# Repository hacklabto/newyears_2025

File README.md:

# Hacky New Years

Hacky New Years is an annual collaborative project, where a hackerspace's 
members produce an artifact in quantity to be sent to other spaces. This can 
be a piece art, electronics, or literature. Whatever the collaborators of 
that year come to consensus on. 

https://knowledge.hacklab.to/wiki/Hacky_New_Years

## Hacklab's artifact for 2025 
A collaborative, interdisciplinary technology based art project.

https://knowledge.hacklab.to/wiki/Hacky_New_Years/2025

This repository contains the software code and other artifacts used in the 
production of the final piece sent for 2025.

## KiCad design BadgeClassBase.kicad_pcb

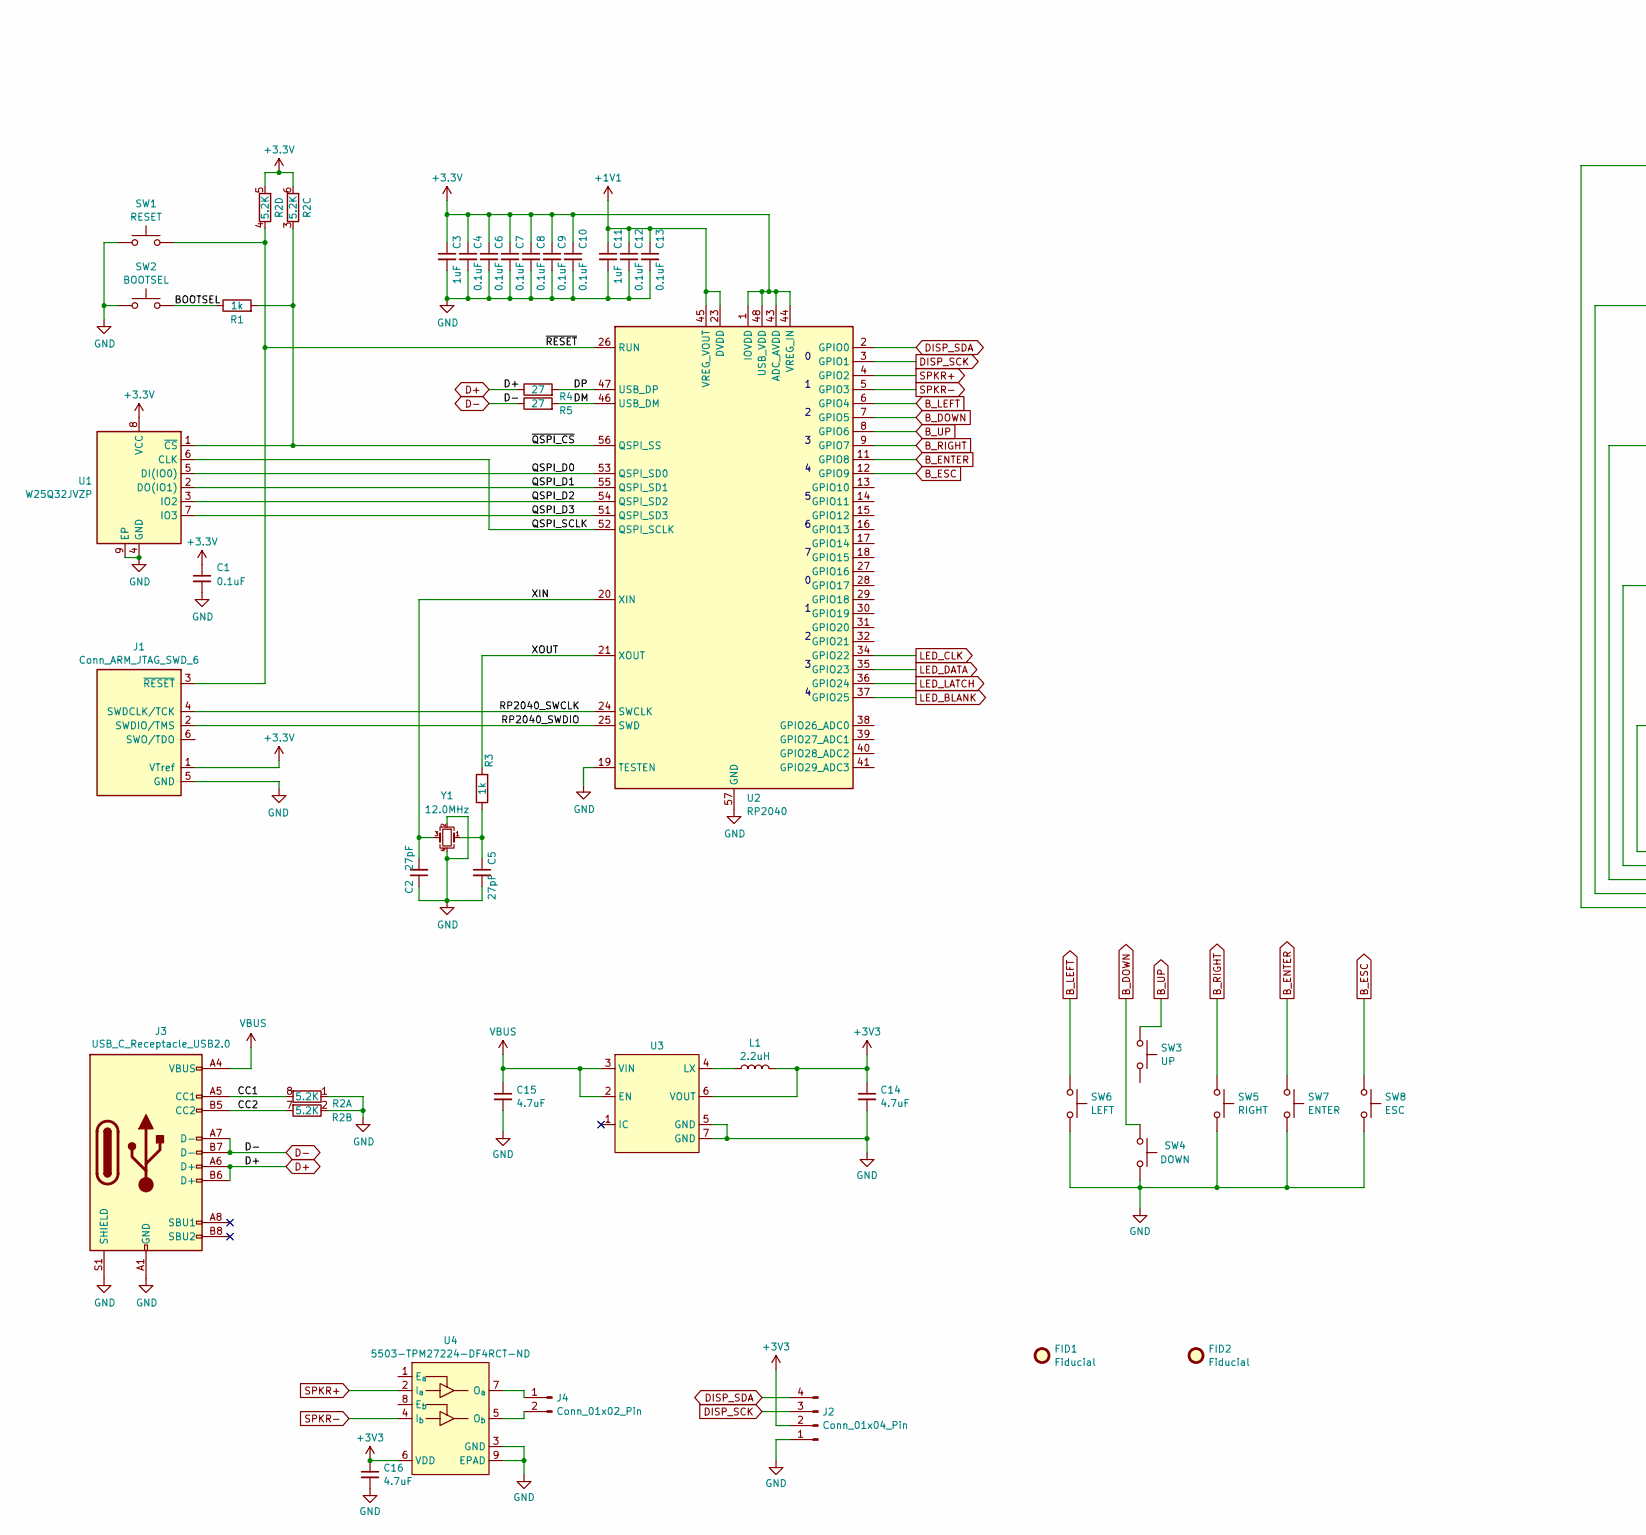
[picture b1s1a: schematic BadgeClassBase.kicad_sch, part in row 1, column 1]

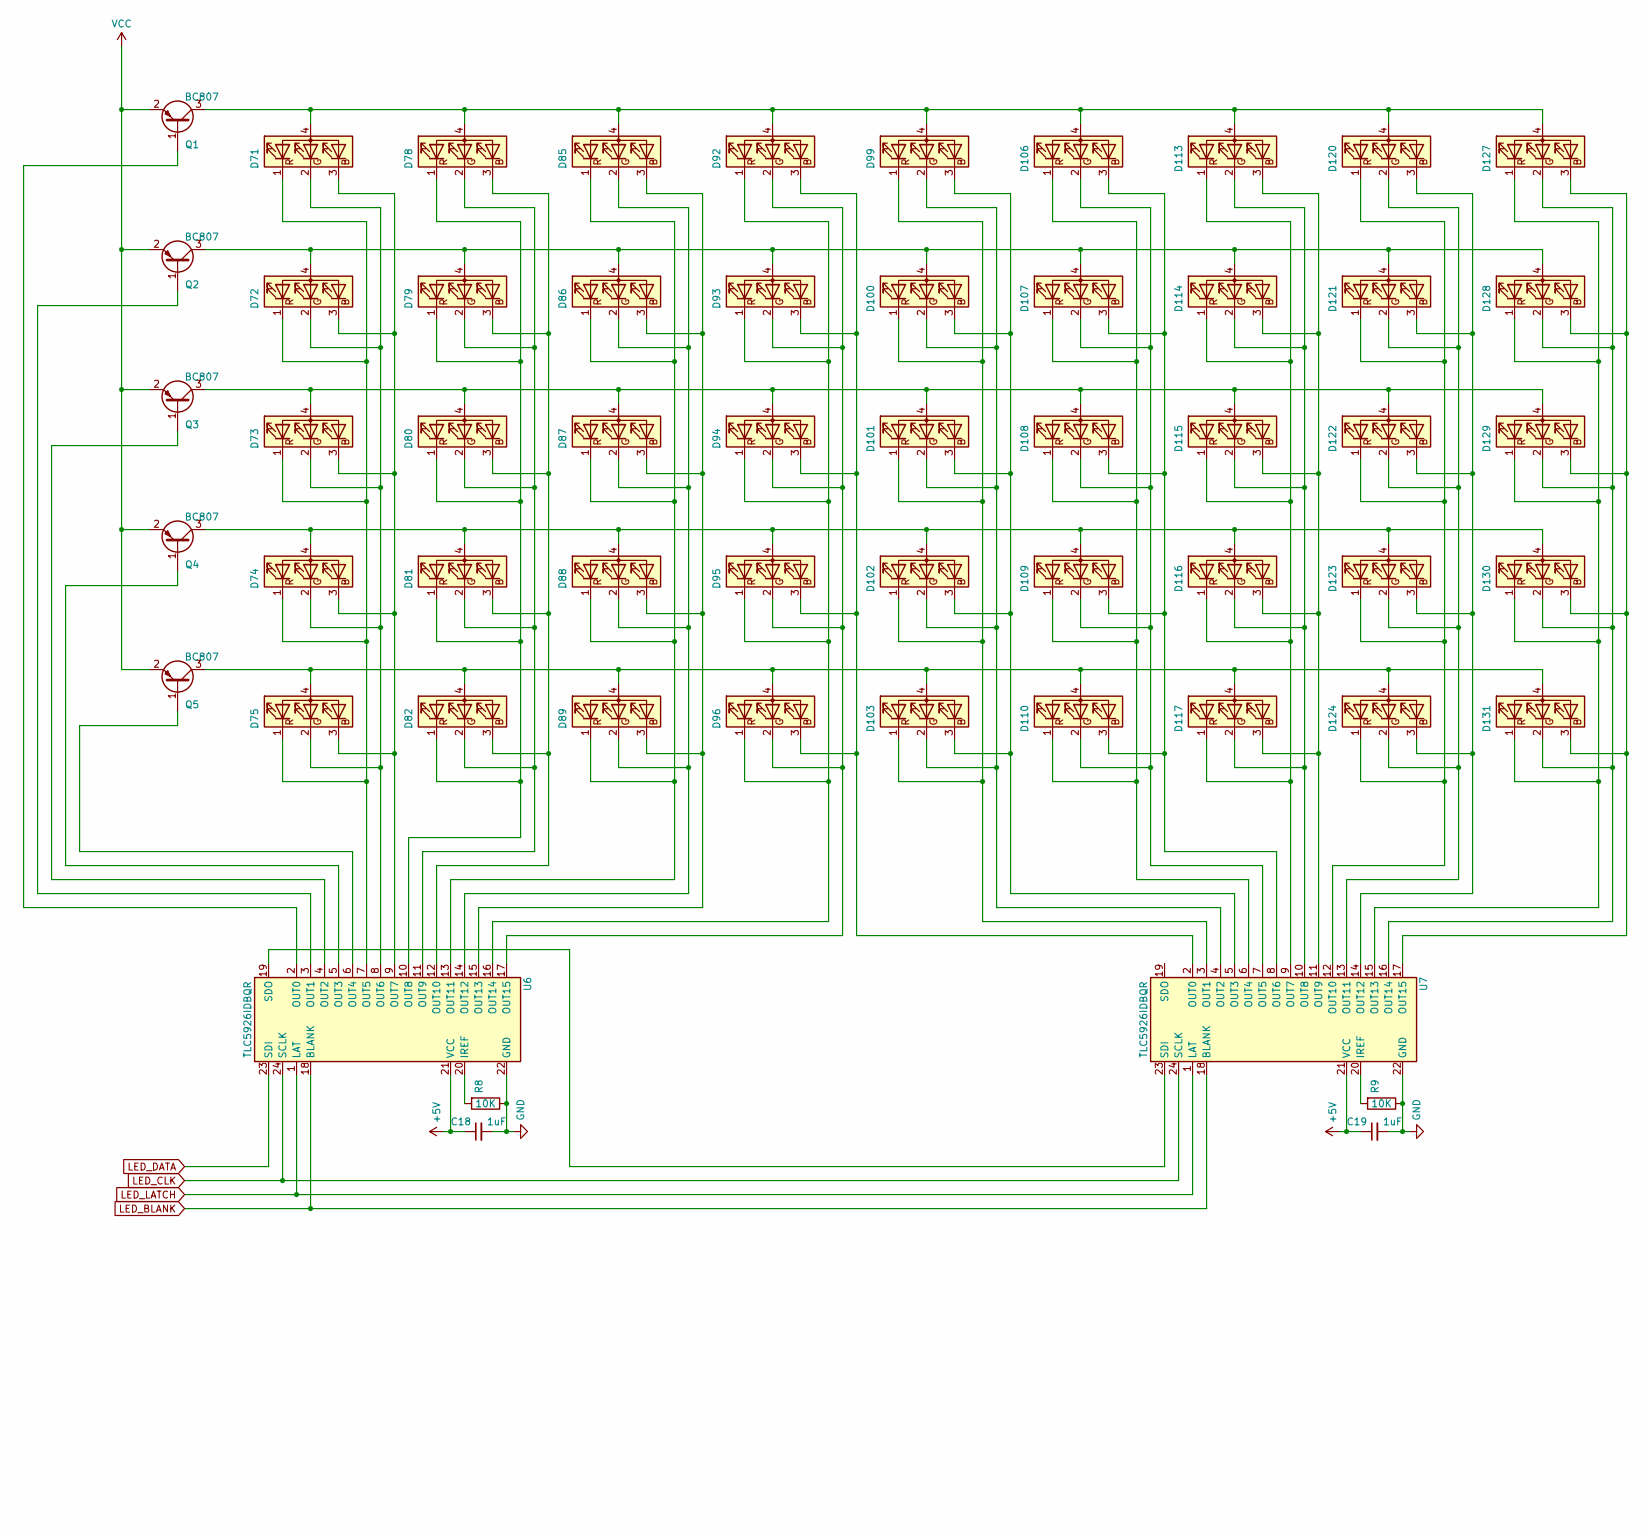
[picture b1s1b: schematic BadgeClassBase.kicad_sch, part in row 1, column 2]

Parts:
C1, C4, C6, C7, C8, C9, C10, C12, C13: 0.1uF; C_0402_1005Metric; Digikey 1276-6844-1-ND
C2, C5: 27pF; C_0402_1005Metric; Digikey 490-12651-1-ND
C3, C11, C18, C19: 1uF; C_0603_1608Metric; Digikey 587-3467-1-ND
C14, C15, C16: 4.7uF; C_0603_1608Metric_Pad1.08x0.95mm_HandSolder
D71, D72, D73, D74, D75, D78, D79, D80, D81, D82, D85, D86, D87, D88, D89, D92, D93, D94, D95, D96, D99, D100, D101, D102, D103, D106, D107, D108, D109, D110, D113, D114, D115, D116, D117, D120, D121, D122, D123, D124, D127, D128, D129, D130, D131: LED_RGBA; LED_RGB_Everlight_EASV3015RGBA0_Horizontal
FID1: Fiducial; SqeakSqeak
FID2: Fiducial; OwO
J1: Conn_ARM_JTAG_SWD_6; Paw-Connect_RevB_TC2030-IDC-NL_2x03_P1.27mm_Vertical
J2: Conn_01x04_Pin; OLED_Display
J3: USB_C_Receptacle_USB2.0; JAE_DX07S016JA1R1500
J4: Conn_01x02_Pin; PinSocket_1x02_P1.27mm_Vertical
L1: 2.2uH; L_0805_2012Metric_Pad1.15x1.40mm_HandSolder
Q1, Q2, Q3, Q4, Q5: BC807; SOT-23
R1, R3: 1k; R_0402_1005Metric
R2: 5.2K; R_Array_Concave_4x0402
R4, R5: 27; R_0402_1005Metric
R8, R9: 10K; R_0603_1608Metric_Pad0.98x0.95mm_HandSolder
SW1: RESET; SW_SPST_TL3342; digikey CKN12215-1-ND
SW2: BOOTSEL; SW_SPST_TL3342; digikey CKN12215-1-ND
SW3: UP; SW_SPST_TL3342; digikey CKN12215-1-ND
SW4: DOWN; SW_SPST_TL3342; digikey CKN12215-1-ND
SW5: RIGHT; SW_SPST_TL3342; digikey CKN12215-1-ND
SW6: LEFT; SW_SPST_TL3342; digikey CKN12215-1-ND
SW7: ENTER; SW_SPST_TL3342; digikey CKN12215-1-ND
SW8: ESC; SW_SPST_TL3342; digikey CKN12215-1-ND
U1: W25Q32JVZP; WSON-8-1EP_6x5mm_P1.27mm_EP3.4x4.3mm
U2: RP2040; QFN-56-1EP_7x7mm_P0.4mm_EP3.2x3.2mm
U3: LFCSP-6-1EP_2x2mm_P0.65mm_EP1.4x0.8mm
U4: WSON-8-1EP_2x2mm_P0.5mm_EP0.9x1.6mm; Digikey 5503-TPM27224-DF4RCT-ND
U6, U7: TLC5926IDBQR; QFN-24-1EP_4x4mm_P0.5mm_EP2.15x2.15mm
Y1: 12.0MHz; Crystal_SMD_SeikoEpson_TSX3225-4Pin_3.2x2.5mm; Digikey RH100-12.000-18-2020-EXT-TR

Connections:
+1V1: C11.1, C12.1, C13.1, U2.23 (DVDD), U2.45 (VREG_VOUT), U2.50 (DVDD)
+3.3V: C1.1, C3.1, C4.1, C6.1, C7.1, C8.1, C9.1, C10.1, J1.1 (VTref), R2.5 (R4.2), R2.6 (R3.2), U1.8 (VCC), U2.1 (IOVDD), U2.10 (IOVDD), U2.22 (IOVDD), U2.33 (IOVDD), U2.42 (IOVDD), U2.43 (ADC_AVDD), U2.44 (VREG_IN), U2.48 (USB_VDD), U2.49 (IOVDD)
+3V3: C14.1, C16.1, J2.2, L1.2, U3.6 (VOUT), U4.6 (VDD)
+5V: C18.1, C19.1, U6.21 (VCC), U7.21 (VCC)
/BOOTSEL: R1.1, SW2.2
/CC1: J3.A5 (CC1), R2.8 (R1.2)
/CC2: J3.B5 (CC2), R2.7 (R2.2)
/DM: R5.2, U2.46 (USB_DM)
/DP: R4.2, U2.47 (USB_DP)
/QSPI_D0: U1.5 (DI(IO0)), U2.53 (QSPI_SD0)
/QSPI_D1: U1.2 (DO(IO1)), U2.55 (QSPI_SD1)
/QSPI_D2: U1.3 (IO2), U2.54 (QSPI_SD2)
/QSPI_D3: U1.7 (IO3), U2.51 (QSPI_SD3)
/QSPI_SCLK: U1.6 (CLK), U2.52 (QSPI_SCLK)
/RP2040_SWCLK: J1.4 (SWDCLK/TCK), U2.24 (SWCLK)
/RP2040_SWDIO: J1.2 (SWDIO/TMS), U2.25 (SWD)
/XIN: C2.2, U2.20 (XIN), Y1.3
/XOUT: R3.2, U2.21 (XOUT)
/~QSPI_CS: R1.2, R2.3 (R3.1), U1.1 (~CS), U2.56 (QSPI_SS)
/~RESET: J1.3 (~RESET), R2.4 (R4.1), SW1.2, U2.26 (RUN)
B_DOWN: SW4.1, U2.7 (GPIO5)
B_ENTER: SW7.1, U2.11 (GPIO8)
B_ESC: SW8.1, U2.12 (GPIO9)
B_LEFT: SW6.1, U2.6 (GPIO4)
B_RIGHT: SW5.1, U2.9 (GPIO7)
B_UP: SW3.1, U2.8 (GPIO6)
D+: J3.A6 (D+), J3.B6 (D+), R4.1
D-: J3.A7 (D-), J3.B7 (D-), R5.1
DISP_SCK: J2.3, U2.3 (GPIO1)
DISP_SDA: J2.4, U2.2 (GPIO0)
GND: C1.2, C2.1, C3.2, C4.2, C5.2, C6.2, C7.2, C8.2, C9.2, C10.2, C11.2, C12.2, C13.2, C14.2, C15.2, C16.2, C18.2, C19.2, J1.5 (GND), J2.1, J3.A1 (GND), J3.B1 (GND), J3.S1 (SHIELD), R2.1 (R1.1), R2.2 (R2.1), R8.1, R9.1, SW1.1, SW2.1, SW4.2, SW5.2, SW6.2, SW7.2, SW8.2, U1.4 (GND), U1.9 (EP), U2.19 (TESTEN), U2.57 (GND), U3.5 (GND), U3.7 (GND), U4.3 (GND), U4.9 (EPAD), U6.22 (GND), U6.25 (GND), U7.22 (GND), U7.25 (GND), Y1.2, Y1.4
LED_BLANK: U2.37 (GPIO25), U6.18 (BLANK), U7.18 (BLANK)
LED_CLK: U2.34 (GPIO22), U6.24 (SCLK), U7.24 (SCLK)
LED_DATA: U2.35 (GPIO23), U6.23 (SDI)
LED_LATCH: U2.36 (GPIO24), U6.1 (LAT), U7.1 (LAT)
unnamed: C5.1, R3.1, Y1.1
unnamed: D71.3 (BK), D72.3 (BK), D73.3 (BK), D74.3 (BK), D75.3 (BK), U6.9 (OUT7)
unnamed: D71.2 (GK), D72.2 (GK), D73.2 (GK), D74.2 (GK), D75.2 (GK), U6.8 (OUT6)
unnamed: D71.1 (RK), D72.1 (RK), D73.1 (RK), D74.1 (RK), D75.1 (RK), U6.7 (OUT5)
unnamed: D78.3 (BK), D79.3 (BK), D80.3 (BK), D81.3 (BK), D82.3 (BK), U6.12 (OUT10)
unnamed: D78.2 (GK), D79.2 (GK), D80.2 (GK), D81.2 (GK), D82.2 (GK), U6.11 (OUT9)
unnamed: D78.1 (RK), D79.1 (RK), D80.1 (RK), D81.1 (RK), D82.1 (RK), U6.10 (OUT8)
unnamed: D85.3 (BK), D86.3 (BK), D87.3 (BK), D88.3 (BK), D89.3 (BK), U6.15 (OUT13)
unnamed: D85.2 (GK), D86.2 (GK), D87.2 (GK), D88.2 (GK), D89.2 (GK), U6.14 (OUT12)
unnamed: D85.1 (RK), D86.1 (RK), D87.1 (RK), D88.1 (RK), D89.1 (RK), U6.13 (OUT11)
unnamed: D92.3 (BK), D93.3 (BK), D94.3 (BK), D95.3 (BK), D96.3 (BK), U7.2 (OUT0)
unnamed: D92.2 (GK), D93.2 (GK), D94.2 (GK), D95.2 (GK), D96.2 (GK), U6.17 (OUT15)
unnamed: D92.1 (RK), D93.1 (RK), D94.1 (RK), D95.1 (RK), D96.1 (RK), U6.16 (OUT14)
unnamed: D72.4 (A), D79.4 (A), D86.4 (A), D93.4 (A), D100.4 (A), D107.4 (A), D114.4 (A), D121.4 (A), D128.4 (A), Q2.3 (C)
unnamed: D99.3 (BK), D100.3 (BK), D101.3 (BK), D102.3 (BK), D103.3 (BK), U7.5 (OUT3)
unnamed: D99.2 (GK), D100.2 (GK), D101.2 (GK), D102.2 (GK), D103.2 (GK), U7.4 (OUT2)
unnamed: D99.1 (RK), D100.1 (RK), D101.1 (RK), D102.1 (RK), D103.1 (RK), U7.3 (OUT1)
unnamed 52: D73.4 (A), D80.4 (A), D87.4 (A), D94.4 (A), D101.4 (A), D108.4 (A), D115.4 (A), D122.4 (A), D129.4 (A), Q3.3 (C); also elsewhere on the board
unnamed: D74.4 (A), D81.4 (A), D88.4 (A), D95.4 (A), D102.4 (A), D109.4 (A), D116.4 (A), D123.4 (A), D130.4 (A), Q4.3 (C)
unnamed: D75.4 (A), D82.4 (A), D89.4 (A), D96.4 (A), D103.4 (A), D110.4 (A), D117.4 (A), D124.4 (A), D131.4 (A), Q5.3 (C)
unnamed: D71.4 (A), D78.4 (A), D85.4 (A), D92.4 (A), D99.4 (A), D106.4 (A), D113.4 (A), D120.4 (A), D127.4 (A), Q1.3 (C)
unnamed: D106.3 (BK), D107.3 (BK), D108.3 (BK), D109.3 (BK), D110.3 (BK), U7.8 (OUT6)
unnamed: D106.2 (GK), D107.2 (GK), D108.2 (GK), D109.2 (GK), D110.2 (GK), U7.7 (OUT5)
unnamed: D106.1 (RK), D107.1 (RK), D108.1 (RK), D109.1 (RK), D110.1 (RK), U7.6 (OUT4)
unnamed 59: D113.3 (BK), D114.3 (BK), D115.3 (BK), D116.3 (BK), D117.3 (BK), U7.11 (OUT9); also elsewhere on the board
unnamed 60: D113.2 (GK), D114.2 (GK), D115.2 (GK), D116.2 (GK), D117.2 (GK), U7.10 (OUT8); also elsewhere on the board
unnamed 61: D113.1 (RK), D114.1 (RK), D115.1 (RK), D116.1 (RK), D117.1 (RK), U7.9 (OUT7); also elsewhere on the board
unnamed: D120.3 (BK), D121.3 (BK), D122.3 (BK), D123.3 (BK), D124.3 (BK), U7.14 (OUT12)
unnamed: D120.2 (GK), D121.2 (GK), D122.2 (GK), D123.2 (GK), D124.2 (GK), U7.13 (OUT11)
unnamed: D120.1 (RK), D121.1 (RK), D122.1 (RK), D123.1 (RK), D124.1 (RK), U7.12 (OUT10)
unnamed: D127.3 (BK), D128.3 (BK), D129.3 (BK), D130.3 (BK), D131.3 (BK), U7.17 (OUT15)
unnamed: D127.2 (GK), D128.2 (GK), D129.2 (GK), D130.2 (GK), D131.2 (GK), U7.16 (OUT14)
unnamed: D127.1 (RK), D128.1 (RK), D129.1 (RK), D130.1 (RK), D131.1 (RK), U7.15 (OUT13)
unnamed: J4.1, U4.7 (O_{a})
unnamed: J4.2, U4.5 (O_{b})
unnamed: Q1.1 (B), U6.2 (OUT0)
unnamed: Q2.1 (B), U6.3 (OUT1)
unnamed: Q3.1 (B), U6.4 (OUT2)
unnamed: Q4.1 (B), U6.5 (OUT3)
unnamed: Q5.1 (B), U6.6 (OUT4)
unnamed: L1.1, U3.4 (LX)
unnamed: R8.2, U6.20 (IREF)
unnamed: U6.19 (SDO), U7.23 (SDI)
unnamed: R9.2, U7.20 (IREF)
SPKR+: U2.4 (GPIO2), U4.2 (I_{a})
SPKR-: U2.5 (GPIO3), U4.4 (I_{b})
VBUS: C15.1, J3.A4 (VBUS), J3.B4 (VBUS), U3.2 (EN), U3.3 (VIN)
VCC: Q1.2 (E), Q2.2 (E), Q3.2 (E), Q4.2 (E), Q5.2 (E)

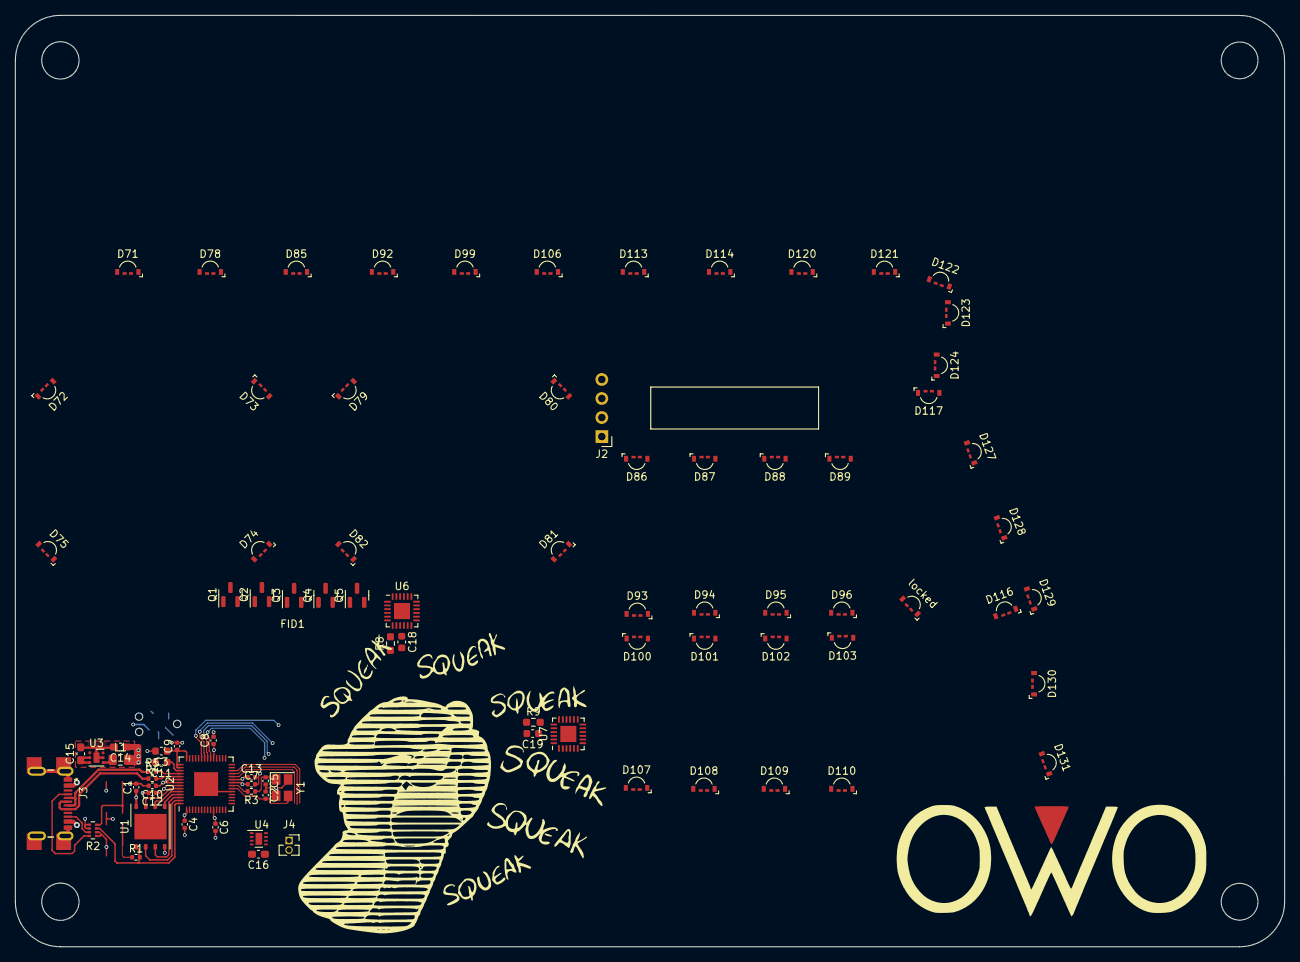
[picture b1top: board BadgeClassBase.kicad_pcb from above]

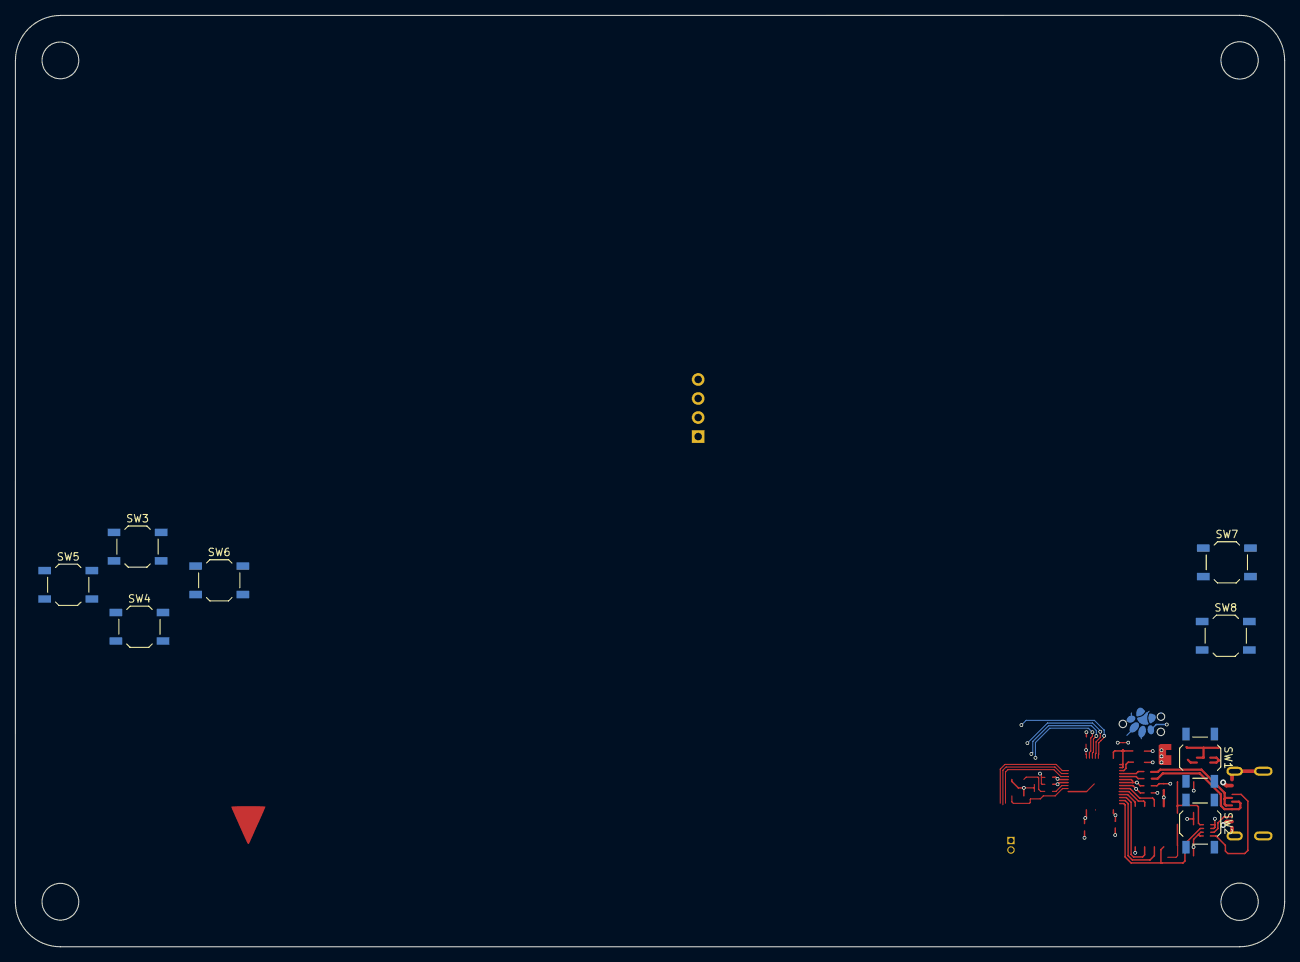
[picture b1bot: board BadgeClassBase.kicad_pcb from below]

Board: 2 copper layers, 169.4 x 124.3 mm, 97 parts (9 on the bottom side), 83 nets.

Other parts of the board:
locked: LED_RGBA; LED_RGB_Everlight_EASV3015RGBA0_Horizontal

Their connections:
unnamed 52: locked.4 (A); also elsewhere on the board
unnamed 59: locked.3 (BK); also elsewhere on the board
unnamed 60: locked.2 (GK); also elsewhere on the board
unnamed 61: locked.1 (RK); also elsewhere on the board

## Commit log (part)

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2025-06-26 Refactor.
2025-06-26 refactor
2025-06-28 Wave tables compile now.
2025-06-29 Setup for doing waves via table lookup. The code needs a lot of cleanup, (lol, constants need to be put into proper variables), but the skeleton is there.
2025-06-29 Constant naming pass.
2025-06-29 More const stuff plus cargo fmt.
2025-06-29 Comment update.
2025-06-30 Begin sketching in adsr envelope.
2025-07-01 Add scale concept to sound sample
2025-07-01 Begin changing square waves to waves with a variable pulse width
2025-07-04 Modify square wave test to make sure the default wave is square.
2025-07-04 Pulse width 50% coming from the pulse width code.
2025-07-04 Unit test consolidation
2025-07-04 Patch in volume interface, which doesn't work right now :(, and test.
2025-07-04 Test volume reduction on table waveform
2025-07-05 ADSR class refomatting.
2025-07-05 Seperate out SoundSourceId and SoundSourceType into their own file.
2025-07-05 Add main pool to has_next call. Also, I probably need to add the concept of an update or I'm going to have problems with mutable borrows.
2025-07-05 Add update and concept of active list (vs free list)
2025-07-05 Get next is no longer mutable.
2025-07-06 Begin work on a sound source messages as a (free) list.
2025-07-08 Message container
2025-07-08 Allow Sound Source update to add to messages.
2025-07-08 Uninitialized sound source are no longer accessable.
2025-07-08 Switch key value type to an enum instead of a raw usize
2025-07-08 Values now have a default
2025-07-10 begin example program.
2025-07-10 Phantom data cleanup
2025-07-10 Sound sources impl now owns its own pools.
2025-07-10 Library now outputs as sine wave.
2025-07-10 Change wave_generator to oscillator, the name used in the midi reference material.
2025-07-10 Init oscillator using a single data packet.
2025-07-10 All oscillator init done in one message.
2025-07-10 Message ID is now optional.
2025-07-11 hook up adsr pool.
2025-07-11 ADS in ADSR coded.
2025-07-11 adsr built + simple test.
2025-07-12 Adding origin to msgs and creating a test help.
2025-07-12 Rename test helper to top. It's probably going to be public.
2025-07-12 Successfully created a sound source through messages and callbacks.
2025-07-12 Have sound sources handle some meta messages.
2025-07-12 Fix test program to use new interfaces.
2025-07-12 amp mixer proof of concept + test.
2025-07-13 Test ADSR waveform with live output.
2025-07-15 Start midi class.
2025-07-16 Midi now included in top global data structure.
2025-07-17 Did some work coding the midi track.
2025-07-19 More track setup.
2025-07-19 Start patching in simple note creation.
2025-07-19 Hooking up and debugging midi.
2025-07-19 So close, but there's silence on the unit test and one of the callbacks isn't triggering.
2025-07-22 Tried different wave form and a slower pace.
2025-07-22 Remove unused messages.
2025-07-22 Remove oscilator key from oscilator messages and refactor oscilator messages.
2025-07-22 More refactoring to remove un-needed keys.
2025-07-22 More key removal?
2025-07-22 Key is removed. The variant already has a key.
2025-07-22 More dead code removal.
2025-07-22 Core sound concept now has a trait.
2025-07-22 More movement toward the idea of a note.
2025-07-22 More spiraling
2025-07-22 amp mixer is not hard coded to adsr and oscilator for testing.
2025-07-23 Passable twink twink little start.
2025-07-24 Remove adsr tests from core functionalty
2025-07-24 Remove generic oscilator completely.
2025-07-24 Remove generic adsr.
2025-07-24 More code removal.
2025-07-24 Unit tests don't go through the sound pool.
2025-07-24 amp_mixer is now simplified.
2025-07-24 Begin making ADSR's arguments templates.
2025-07-24 Init more consistent. Added note off to core sound sources.
2025-07-24 Pulse width is now an oscilator template
2025-07-24 Volume is now compile time on oscilators.
2025-07-24 Oscilator type is now a compile time constant.
2025-07-24 More compile time coding
2025-07-24 Give T a more unique name as prep for removing it
2025-07-24 Simplify adsr, mostly.
2025-07-24 Build wave tables from ints now.
2025-07-24 Begin removing to_u16
2025-07-24 RIP to_u16
2025-07-24 wave tables now go from -0x8000 to 0x8000
2025-07-24 Unit test reference values shame me less.
2025-07-24 Adsr code almost looks readable.
2025-07-24 Everything is tree like now.
2025-07-24 update and get at the same time for core sound trait implementers
2025-07-24 More code removed.
2025-07-24 Rip messages, killed by a simpler data ownership scheme.
2025-07-24 Rip top
2025-07-24 RIP sound source pools. The freelist probably lives to see another day.
2025-07-24 Rip flexible/ modular sound sources.
2025-07-25 Adsr accepts times in ms now.
2025-07-25 Fixed state/ divide by 0 bug in adsr.
2025-07-26 Double oscillator done
2025-07-26 Remove lifetime from midi structures by declaring the SMF separately and borrowing it when I want to get the next sound sample.
2025-07-26 Default oscillator reset to do nothing for non-oscillators.
2025-07-26 Note is now a wrapper for the one instrument I have,
2025-07-27 Semi credible piano sounds.
2025-07-27 Reformat ADSR generic arguments
2025-07-27 adsr fixed.
2025-07-27 Checking in experimental adsr. experimental, like broke.
2025-07-27 Adsr progressed.
2025-07-28 init -> note.
2025-07-28 Get tests working again.
2025-07-28 Removed a lot of default traits.
2025-07-28 Make it easier to switch to the guitar test case.
2025-07-29 Midi playback improved a bit by being sligtly more correct.
2025-07-29 Remove ignore hack
2025-07-29 Define number of notes in midi generic instead of hard coding it.
2025-07-29 switch test case to vivaldi.
2025-07-29 Check in vivaldi source file
2025-07-29 Add inines.
2025-07-30 Fixed sound, sort of, by filtering after the ADSR envelope is done.
2025-07-30 Compile time filter parameter calculation.
2025-07-30 filters now compute parameters at compile time.
2025-07-30 Filter unit tests and stuff.
2025-07-31 Filters now behave like they should
2025-07-31 Improve stuff. Honest.
2025-07-31 More tests.
2025-07-31 channels in midi structure.
2025-07-31 More instrument prototypes.
2025-07-31 More work on instruments.
2025-07-31 Re-enable nostd - I'm not debugging anymore. Work on midi timing.
2025-07-31 Encode the rate we're going through the midi file as a fraction.
2025-07-31 I'm able to fast forward through the midi file to get a good idea what the loudest sound sample is.
2025-07-31 midi player more or less alpha worthy
2025-08-01 Start patching in midi library to rpi
2025-08-01 Slowly integrating the new midi code.
2025-08-01 Have trivial example report memory usage.
2025-08-01 Successful midi play on the Pico.
2025-08-01 amp_adders fields are private. Preps the way for doing a format conversion later.
2025-08-01 Break tracks out of midi.
2025-08-01 Break out events.
2025-08-01 Midi parse should no longer need an allocator.
2025-08-01 Try vivaldi
2025-08-02 A series of small runtime optimization that didn't seem to buy much.
2025-08-02 Add update, add to amp_adder.
2025-08-02 Improve efficency (I hope) in the get_next() path.
2025-08-02 Reduce overhead of playing silence.
2025-08-02 Propegate update concept. Refactor ADSR so it computes envelope values less frequently.
2025-08-02 Another dirty micro-optimization. Don't divide final output of amp_adder to save a few cycles.
2025-08-02 Integrate with changes to midi library.
2025-08-02 Have adsr be a wrapper in preparation for a future optimization.
2025-08-02 Remove multiply.
2025-08-02 Remove noise at silence by not adding 0x80 to PWM output.
2025-08-02 Various faster PWM configurations.
2025-08-02 Some shameful but clever optimizations.
2025-08-02 Remove some cleverness.
2025-08-03 Entertainer and fixed some midi playback corner cases.
2025-08-03 One step toward frequency filters with cutoffs that can be set in the constructor.
2025-08-03 Pass filter cutoff in via new
2025-08-03 Got rid of sometime clicking noise by having the ADSR send out 10 ms of silence when done.
2025-08-03 Reduce CPU usage
2025-08-04 Cello update and test song.
2025-08-04 Cello experimentation
2025-08-04 Create the idea of a generic instrument template
2025-08-04 Use new template for electric piano
2025-08-04 Move low pass filter calculators to once place so I can reuse them
2025-08-04 Add guitar test case.
2025-08-04 More instruments.
2025-08-04 Update oboe and add a path so I can test specific instruments even when the midi file is for them, but defaults to, say piano.
2025-08-04 I wouldn't say it's a good french horn, but it is a french horn.
2025-08-04 Horn test
2025-08-04 Piano tuning.
2025-08-05 Compute tan at compile time using the const soft float library. Compiles 10x slower, but the code is 10x less gross, so win?
2025-08-05 Fixes for comile problems with the const_float crate.
2025-08-05 switch piosound assembly to pull
2025-08-05 And this actually works.
2025-08-06 Change playback song.
2025-08-06 Break float tan out from int tan.
2025-08-06 Switch filter co-efficient calculator to floating point, which is less gross than fixed point.
2025-08-06 Cut maximum of oscillators in half. This means each oscillator will range from -0.5 to 0.5, and double oscillators will range from -1.0 to 1.0.
    The oscillators feed into the low pass filter, so this makes the low pass filter's fixed point math a bit easier to reason about, in the sense that the input is always between "-1" and "1"
2025-08-07 Switch i64 to i32 on filter. Seems to produce good results. Docuementation.
2025-08-07 Add second DMA buffer resource to PioSound so I can try chaining two buffers.
2025-08-07 audio playback moved.
2025-08-08 More clean up
2025-08-08 cargo fmt
2025-08-08 Remove extra DMA channel - things seem to be working as is.
2025-08-08 Small filter change.
2025-08-09 Martial Display resources into a the Core0 resource class.
2025-08-09 More refactoring
2025-08-09 More more resources into core1 bundle.
2025-08-09 Sound on PIO 1
2025-08-09 Hard bind piosound to PIO0. It's not as elegant as something more flexible, but it makes binding the interrupt handler easier.
2025-08-09 Backlight hard bound to pio1
2025-08-10 Make core0 and core1 resources more concrete
2025-08-10 Begin to refactor code to be more like the multicore example.
2025-08-10 Sound plaback on core 1 now.
2025-08-11 Add static assert for dither
2025-08-11 Remove unused packages, pass 1
2025-08-11 Update more crates.
2025-08-11 Embassy rp moved up one version.
2025-08-12 Disable sound and backlight while I move versions up
2025-08-12 Sound advanced to embassy-rp-0.4.0
2025-08-12 Advance to embassy-rp 0.5 with everything but the sound.
2025-08-12 Upgrade to embassy-rp 0.6. One more to go.
2025-08-12 Change 8 bit DMA transfers to 32 bit DMA transfers. Stops DMA buffer from emptying.
2025-08-14 Restructuring pio code to pulse "positive" and "negative"
2025-08-14 Check point commit. I think both the positive and negative paths work on the sound output
2025-08-15 backlight compiles again. Added some comments.
2025-08-15 Restore default levels for PIO pins
2025-08-15 Switch PIO sound to playback that adds more noise but doesn't butcher low frequency notes as much
2025-08-15 Remove config from PIO. Some of these values are rightly tied to compile time constants, like "the size of the shift register on the circuit"
2025-08-16 Split out backlight device.
2025-08-16 Begin setting up backlight triple buffer.
2025-08-16 Code to update the DMA buffer for the LED backlights (untested)
2025-08-16 User driver for the LED. Testing and debugging on the driver back end.
2025-08-17 Change priority on the backled DMA packet launcher executor to high.
2025-08-18 Interface to get information about midi notes current playing + some documentation for sound buffer playback length
2025-08-29 Documentation status update
2025-08-31 Documentation
2026-05-13 Start to change the sound library in example so it works with more linux distributions.
2026-05-13 Sample ends semi-gracefully when the song is over (there is a click)
2026-05-19 temp rename file.
2026-05-19 Rename x
2026-05-19 Final rename. Original historu preserved on hardware with git log --follow.
2026-06-26 Kick off meeting changes. Enable negative PWM in pio code, but keep the output positive.
